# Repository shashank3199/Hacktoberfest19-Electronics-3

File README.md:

# Electronics-3

## Introduction
This repository contains the board design for Multiplexing 4 Line Sensing Array Modules: LSA08 (reference [here](https://www.cytron.io/p-lsa08)) to a single pair of Full Duplex Serial Lines and Analog Reading Values.

## Layout

### Board File -

### Schematic File -

## Files in the Repository
The files in the repository are :

#### LSA-PCB 4xSerial+Analog.brd
This is the Board file and contains the Blueprint of the Shield Layout (Prototype).

#### LSA-PCB 4xSerial+Analog.sch
This is the Schematic file and contains the actual circuitary behind the Shield.

#### README.md
The Description file containing details about the repository. The file that you looking at right now.

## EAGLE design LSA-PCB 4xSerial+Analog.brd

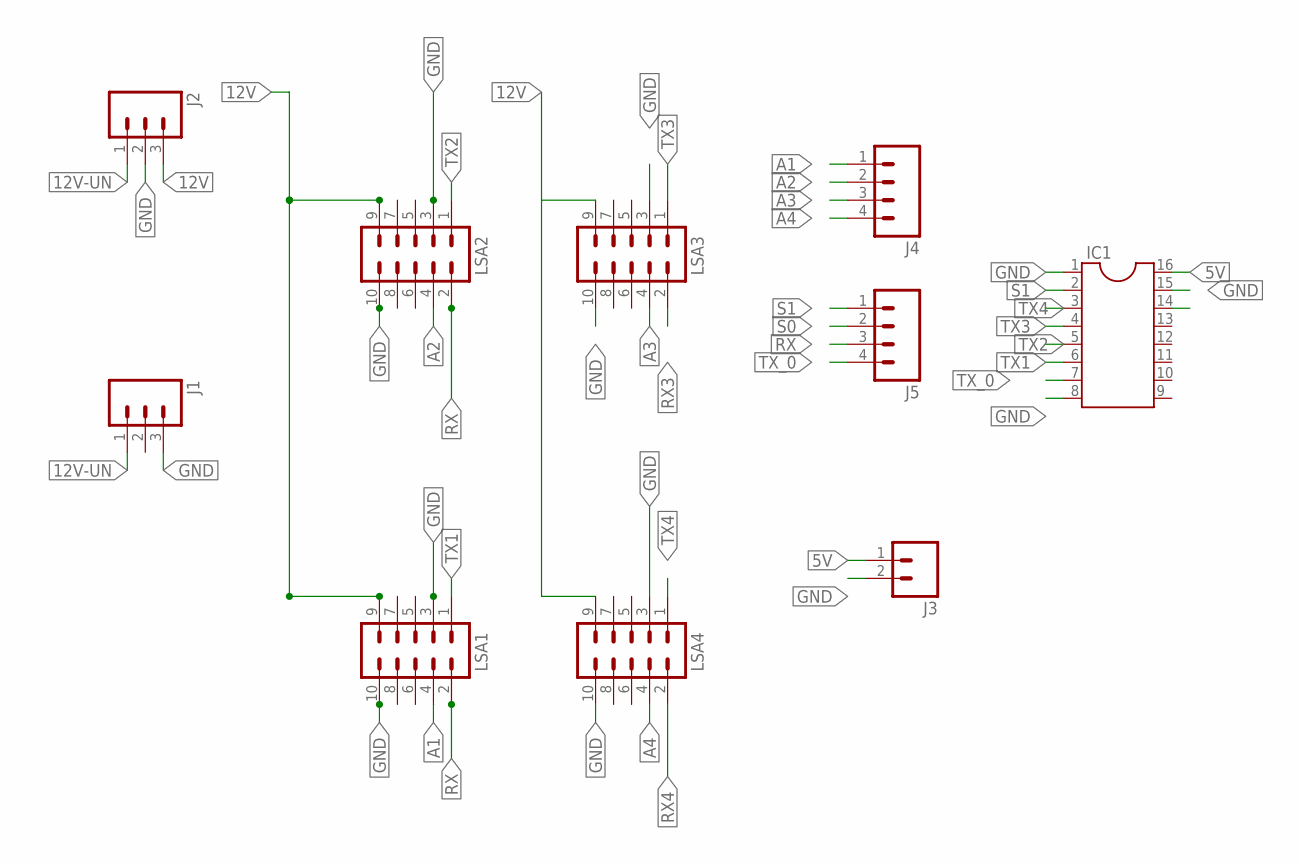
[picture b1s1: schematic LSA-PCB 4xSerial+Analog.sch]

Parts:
IC1: DIL16S; SOCKET-16
J1, J2: M03PTH; 1X03
J3: M02PTH; 1X02
J4, J5: M04PTH; 1X04
LSA1, LSA2, LSA3, LSA4: M05X2SHD_LOCK; 2X5-SHROUDED_LOCK

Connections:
5V: IC1.16, J3.1
12V: J2.3, LSA1.9, LSA2.9, LSA3.9, LSA4.9
12V-UN: J1.1, J2.1
A1: J4.1, LSA1.4
A2: J4.2, LSA2.4
A3: J4.3, LSA3.4
A4: J4.4, LSA4.4
GND: IC1.1, IC1.8, IC1.15, J1.3, J2.2, J3.2, LSA1.3, LSA1.10, LSA2.3, LSA2.10, LSA3.3, LSA3.10, LSA4.3, LSA4.10
RX: J5.3, LSA1.2, LSA2.2
RX3: LSA3.2
RX4: LSA4.2
S0: IC1.14, J5.2
S1: IC1.2, J5.1
TX1: IC1.6, LSA1.1
TX2: IC1.5, LSA2.1
TX3: IC1.4, LSA3.1
TX4: IC1.3, LSA4.1
TX_0: IC1.7, J5.4

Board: 2 copper layers, 10 parts (0 on the bottom side), 16 nets, no tracks yet.

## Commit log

2019-10-02 comet3
2019-10-20 Added Documentation
2019-10-20 Fixed Documentation

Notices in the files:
parts and their libraries:
SparkFun-Connectors: Licensing: Creative Commons ShareAlike 4.0 International - https://creativecommons.org/licenses/by-sa/4.0
